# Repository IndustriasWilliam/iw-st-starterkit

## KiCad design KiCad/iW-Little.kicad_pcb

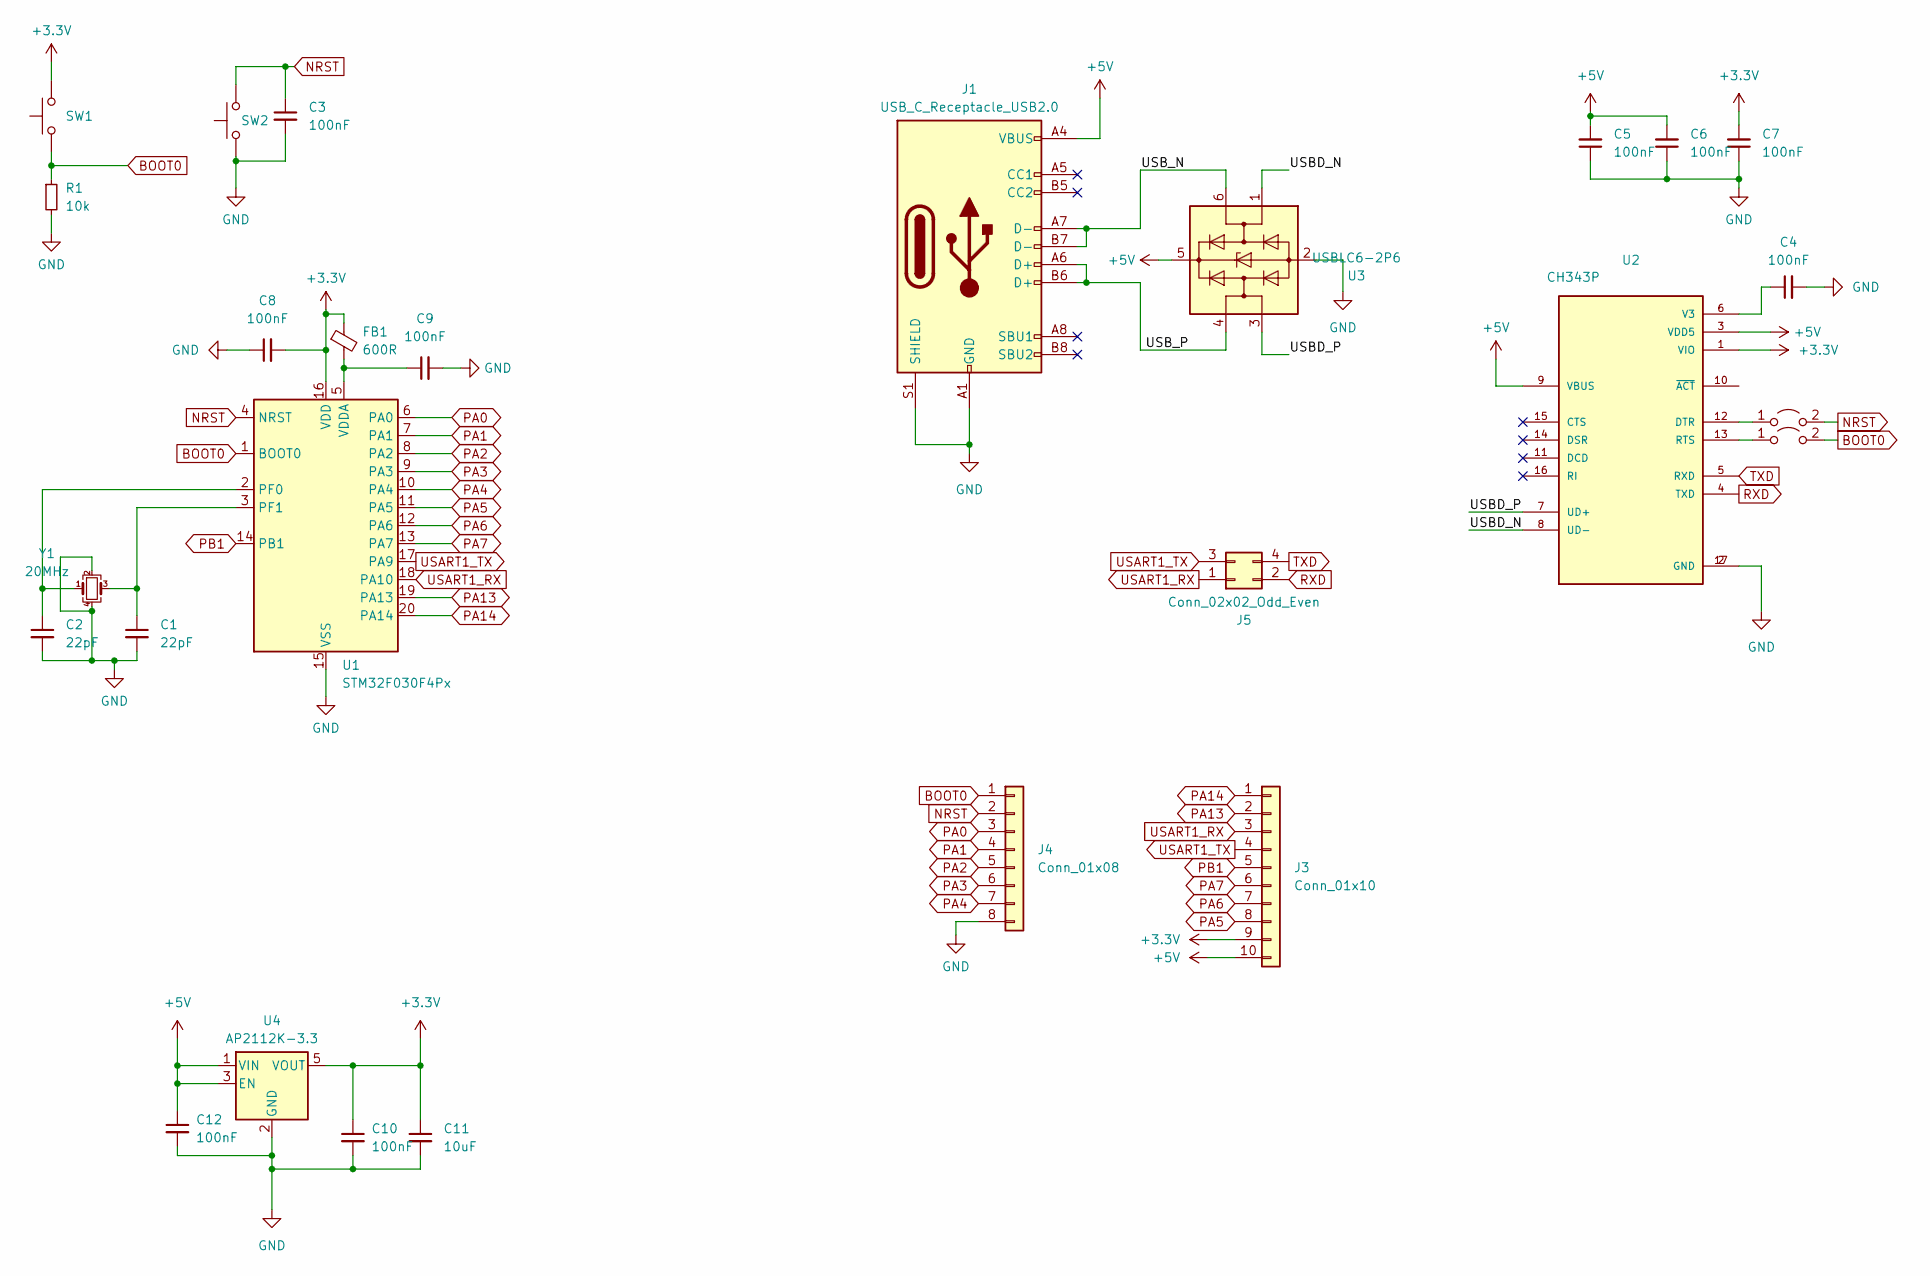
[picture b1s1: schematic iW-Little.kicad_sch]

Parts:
C1, C2: 22pF; C_0603_1608Metric
C3, C4, C5, C6, C7, C8, C9, C10, C12: 100nF; C_0603_1608Metric
C11: 10uF; C_0603_1608Metric
FB1: 600R; L_0603_1608Metric
J1: USB_C_Receptacle_USB2.0; USB_C_Receptacle_Palconn_UTC16-G
J3: Conn_01x10; PinHeader_1x10_P2.54mm_Vertical
J4: Conn_01x08; PinHeader_1x08_P2.54mm_Vertical
J5: Conn_02x02_Odd_Even; PinHeader_2x02_P2.54mm_Vertical
JP1, JP2: Jumper_2_Open; SolderJumper-2_P1.3mm_Open_TrianglePad1.0x1.5mm
R1: 10k; R_0603_1608Metric
SW1, SW2: SW_Push; SW_SPST_B3U-1000P
U1: STM32F030F4Px; TSSOP-20_4.4x6.5mm_P0.65mm
U2: CH343P; QFN50P300X300X80-17N; PARTREV 1E
U3: USBLC6-2P6; SOT-666
U4: AP2112K-3.3; SOT-23-5
Y1: 20MHz; Crystal_SMD_3225-4Pin_3.2x2.5mm

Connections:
+3.3V: C7.2, C8.2, C10.1, C11.1, FB1.1, J3.9, SW1.2, U1.16 (VDD), U2.1 (VIO), U4.5 (VOUT)
+5V: C5.2, C6.2, C12.1, J1.A4 (VBUS), J1.A9 (VBUS), J1.B4 (VBUS), J1.B9 (VBUS), J3.10, U2.3 (VDD5), U2.9 (VBUS), U3.5 (VBUS), U4.1 (VIN), U4.3 (EN)
/USBD_N: U2.8 (UD-), U3.1 (I/O1)
/USBD_P: U2.7 (UD+), U3.3 (I/O2)
/USB_N: J1.A7 (D-), J1.B7 (D-), U3.6 (I/O1)
/USB_P: J1.A6 (D+), J1.B6 (D+), U3.4 (I/O2)
BOOT0: J4.1, JP2.2 (B), R1.1, SW1.1, U1.1 (BOOT0)
GND: C1.2, C2.2, C3.2, C4.2, C5.1, C6.1, C7.1, C8.1, C9.2, C10.2, C11.2, C12.2, J1.A1 (GND), J1.A12 (GND), J1.B1 (GND), J1.B12 (GND), J1.S1 (SHIELD), J4.8, R1.2, SW2.1, U1.15 (VSS), U2.2 (GND), U2.17 (GND), U3.2 (GND), U4.2 (GND), Y1.2, Y1.4
NRST: C3.1, J4.2, JP1.2 (B), SW2.2, U1.4 (NRST)
unnamed: JP1.1 (A), U2.12 (DTR)
unnamed: JP2.1 (A), U2.13 (RTS)
unnamed: C2.1, U1.2 (PF0), Y1.1
unnamed: C1.1, U1.3 (PF1), Y1.3
unnamed: C9.1, FB1.2, U1.5 (VDDA)
unnamed: C4.1, U2.6 (V3)
PA0: J4.3, U1.6 (PA0)
PA1: J4.4, U1.7 (PA1)
PA2: J4.5, U1.8 (PA2)
PA3: J4.6, U1.9 (PA3)
PA4: J4.7, U1.10 (PA4)
PA5: J3.8, U1.11 (PA5)
PA6: J3.7, U1.12 (PA6)
PA7: J3.6, U1.13 (PA7)
PA13: J3.2, U1.19 (PA13)
PA14: J3.1, U1.20 (PA14)
PB1: J3.5, U1.14 (PB1)
RXD: J5.2, U2.4 (TXD)
TXD: J5.4, U2.5 (RXD)
USART1_RX: J3.3, J5.1, U1.18 (PA10)
USART1_TX: J3.4, J5.3, U1.17 (PA9)

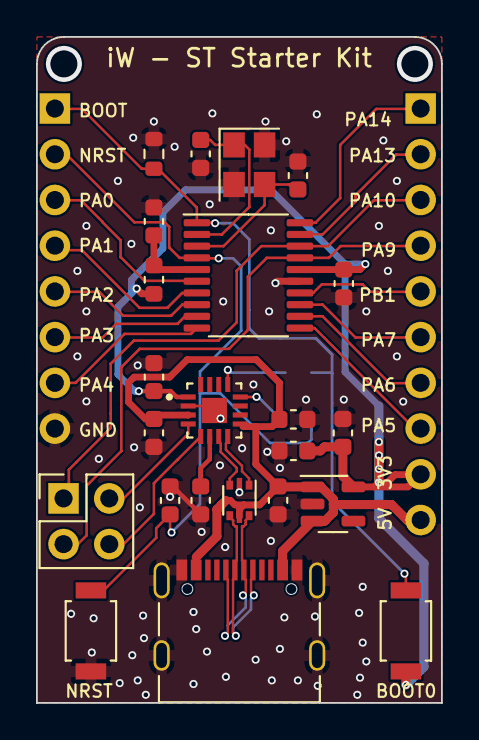
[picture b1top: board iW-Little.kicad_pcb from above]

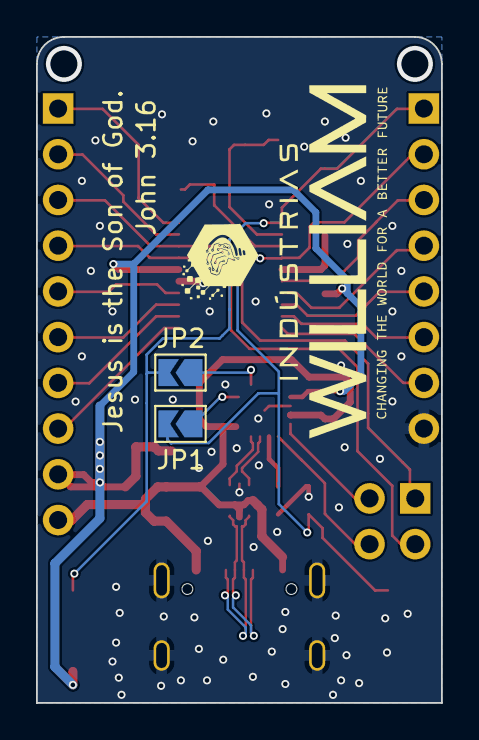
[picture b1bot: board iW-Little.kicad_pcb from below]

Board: 11 copper layers, 22.5 x 37.0 mm, 27 parts (2 on the bottom side), 30 nets.

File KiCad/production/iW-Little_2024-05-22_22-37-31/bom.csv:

Designator,Footprint,Quantity,Value,LCSC Part #
"C1, C2",0603,2,22pF,
"C10, C12, C3, C4, C5, C6, C7, C8, C9",0603,9,100nF,
C11,0603,1,10uF,
FB1,0603,1,600R,
J1,USB_C_Receptacle_Palconn_UTC16-G,1,USB_C_Receptacle_USB2.0,
R1,0603,1,10k,
"SW1, SW2",SW_SPST_B3U-1000P,2,SW_Push,
U1,TSSOP-20_4.4x6.5mm_P0.65mm,1,STM32F030F4Px,
U3,SOT-666,1,USBLC6-2P6,
U4,SOT-23-5,1,AP2112K-3.3,
Y1,Crystal_SMD_3225-4Pin_3.2x2.5mm,1,20MHz,

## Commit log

2025-02-17 size changed
